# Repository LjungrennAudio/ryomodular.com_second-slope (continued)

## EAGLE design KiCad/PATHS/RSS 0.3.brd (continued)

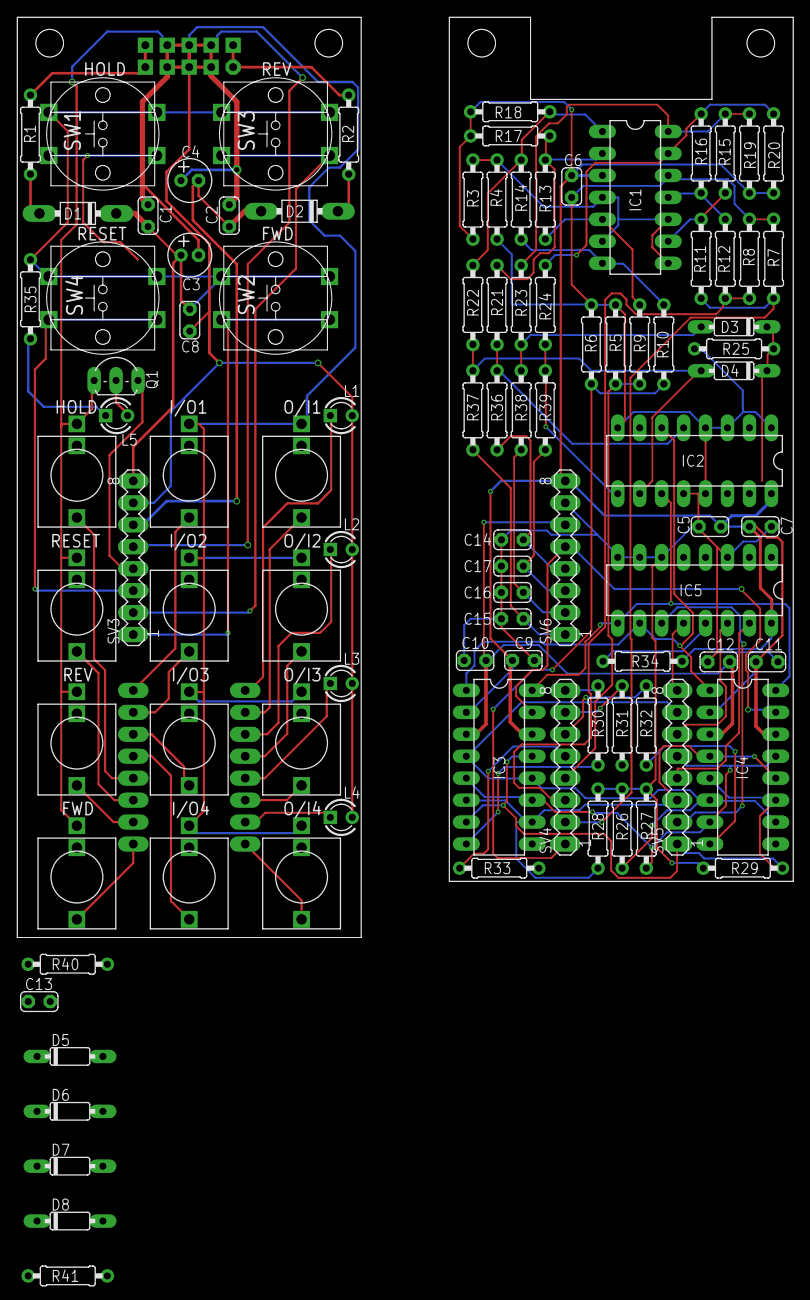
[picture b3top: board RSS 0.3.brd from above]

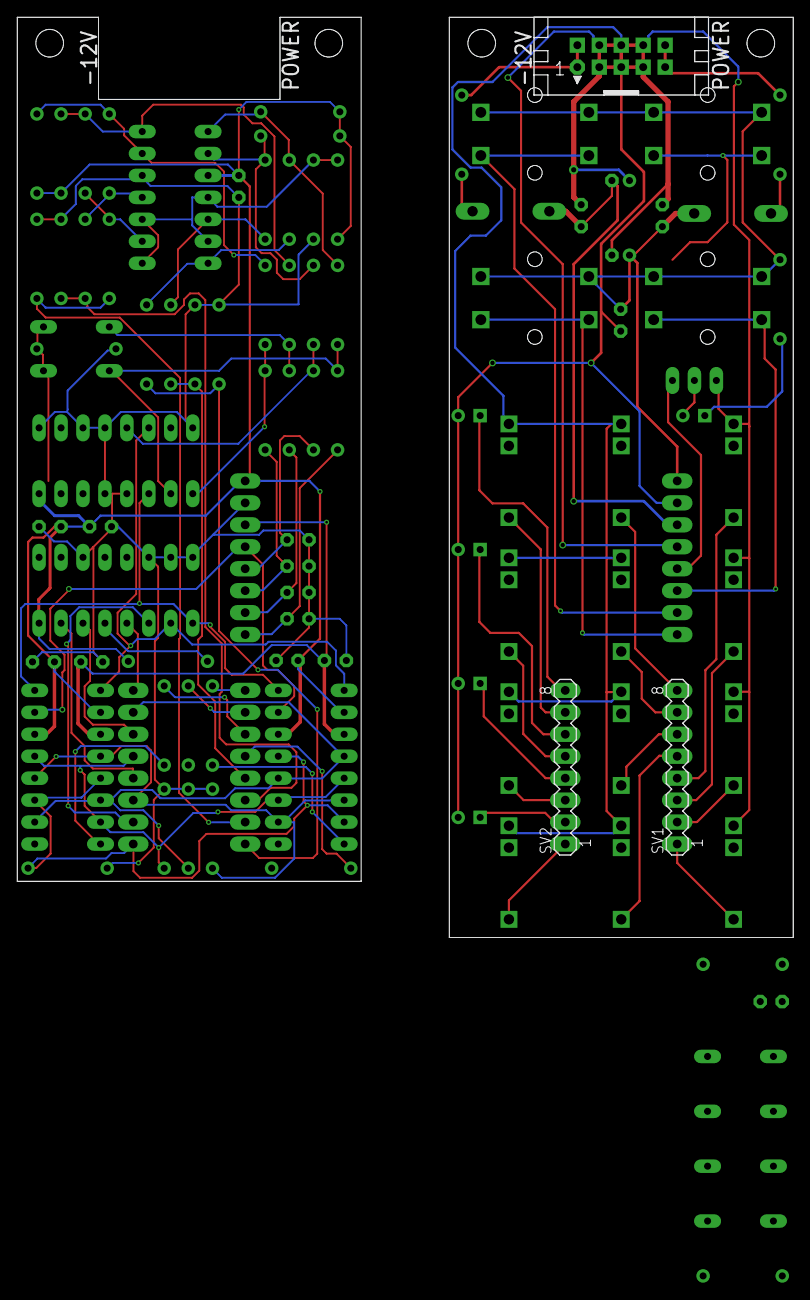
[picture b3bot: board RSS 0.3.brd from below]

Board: 2 copper layers, 89.8 x 106.5 mm, 100 parts (3 on the bottom side), 73 nets.

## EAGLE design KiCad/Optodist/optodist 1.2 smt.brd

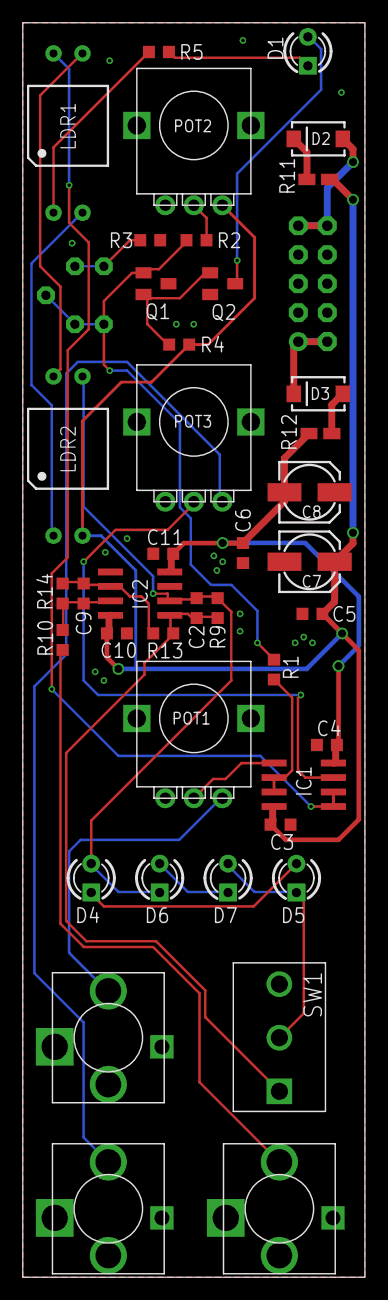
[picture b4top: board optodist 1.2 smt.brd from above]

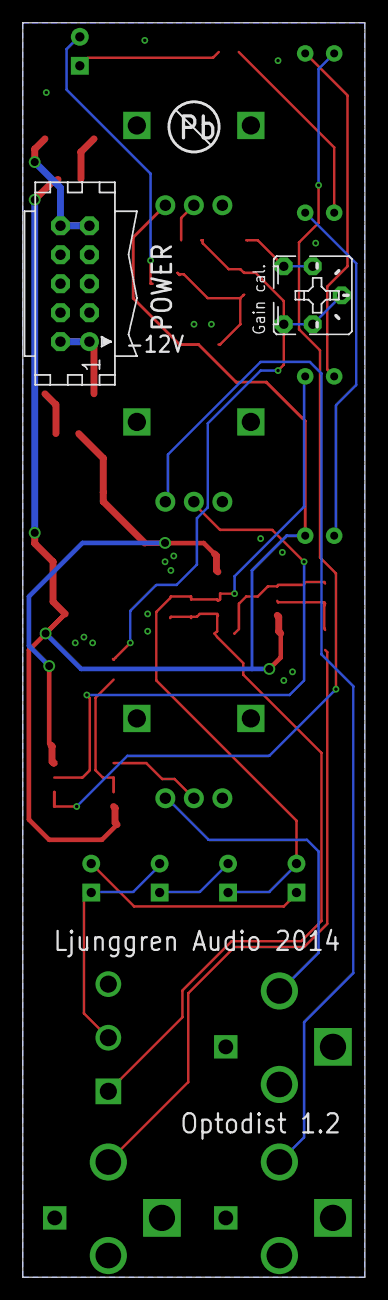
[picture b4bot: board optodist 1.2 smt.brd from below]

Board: 2 copper layers, 30.0 x 110.0 mm, 43 parts (2 on the bottom side), 30 nets.

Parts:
C2, C9: 100pF; C0603K
C3, C4, C5, C6, C10, C11: 100nF; C0603K
C7, C8: 10uF; 153CLV-0505
CV: ERTHENVAR_3.5MM_JACKHOLES; ERTHENVAR
D1, D4, D5, D6, D7: LED3MM
D2, D3: SB130; SMA-DIODE
IC1, IC2: TL072; SO08
IN: ERTHENVAR_3.5MM_JACKHOLES; ERTHENVAR
LDR1, LDR2: SR2/SR3; VTL5C
OUT: ERTHENVAR_3.5MM_JACKHOLES; ERTHENVAR
POT1: 100K lin; POT-ALPHA9
POT2: 25K lin; POT-ALPHA9
POT3: 100K log; POT-ALPHA9
POWER: CON10L
Q1: BC857B; SOT23-BEC
Q2: BC847B; SOT23
R1, R9: 68K; C0603K
R2: 100K; C0603K
R3: 100R; C0603K
R4: 4.7M; C0603K
R5, R10: 1K; C0603K
R11, R12: 10R; R0805W
R13, R14: 10K; C0603K
SW1: ON-OFF; SPDT-HORIZONTAL-TOP-SUBMINI-MULTICOMP
TRIM1: 2K; B25P

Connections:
0V: C3.2, C4.1, C5.2, C6.1, C7.-, C8.+, C10.2, C11.1, CV.RING1, CV.RING2, IC2.3, IC2.5, IN.RING1, IN.RING2, OUT.RING1, OUT.RING2, POT1.GND$1, POT1.GND$2, POT1.LEFT, POT2.GND$1, POT2.GND$2, POT2.LEFT, POT3.GND$1, POT3.GND$2, POT3.LEFT, POWER.3, POWER.4, POWER.5, POWER.6, POWER.7, POWER.8, Q1.C, Q2.2, R3.1
+12V: C3.1, C5.1, C7.+, C10.1, IC1.8, IC2.8, LDR2.2, POT2.RIGHT, R4.2, R11.2
-12V: C4.2, C6.2, C8.-, C11.2, IC1.4, IC2.4, R12.2
AUDIO_IN: IC1.3, POT3.MID
AUDIO_OUT: C2.2, IC2.1, R9.1, R13.1, SW1.1
CV_IN: D1.A, R5.1
unnamed: IC1.6, IC1.7, R1.1
unnamed: POT2.MID, R2.1
unnamed: Q1.B, R1.2, R2.2, TRIM1.E, TRIM1.EE, TRIM1.S
unnamed: Q1.E, Q2.1, R4.1
unnamed: CV.TIP, POT1.RIGHT
unnamed: D1.K, Q2.3
unnamed: R3.2, TRIM1.A, TRIM1.AA
unnamed: IN.TIP, POT3.RIGHT
unnamed: OUT.TIP, R10.2
unnamed: IC1.1, IC1.2, LDR1.3
unnamed: D2.C, R11.1
unnamed: C2.1, D4.K, D6.A, IC2.2, LDR2.4, R9.2
unnamed: LDR1.1, R5.2
unnamed: LDR1.2, LDR2.1
unnamed: LDR1.4, LDR2.3
unnamed: D3.A, R12.1
unnamed: C9.2, IC2.7, R10.1, R14.2
unnamed: D3.C, POWER.1, POWER.2
unnamed: D2.A, POWER.9, POWER.10
unnamed: C9.1, IC2.6, R13.2, R14.1
unnamed: IC1.5, POT1.MID
unnamed: D4.A, D5.K
unnamed: D6.K, D7.A
unnamed: D5.A, D7.K, SW1.2

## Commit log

2024-08-30 init commit of second slope...
    yup, it's another module unlikely to ever be published or released in the state it's seen here! btu this is such wonderful analogue logic goodness it's absolutely sure to find light _somewhere_
2024-08-31 further init files added
    yup, moar!
2025-01-13 filing
